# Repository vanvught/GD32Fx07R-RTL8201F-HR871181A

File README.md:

# GD32Fx07R development board with RTL8201F and HR871181A

This board can be used with the `GD32F107Rx` , `GD32F207Rx`, `GD32F407Rx` MCU's. 

More information [https://www.gd32-dmx.org/dev-board.html](https://www.gd32-dmx.org/dev-board.html)

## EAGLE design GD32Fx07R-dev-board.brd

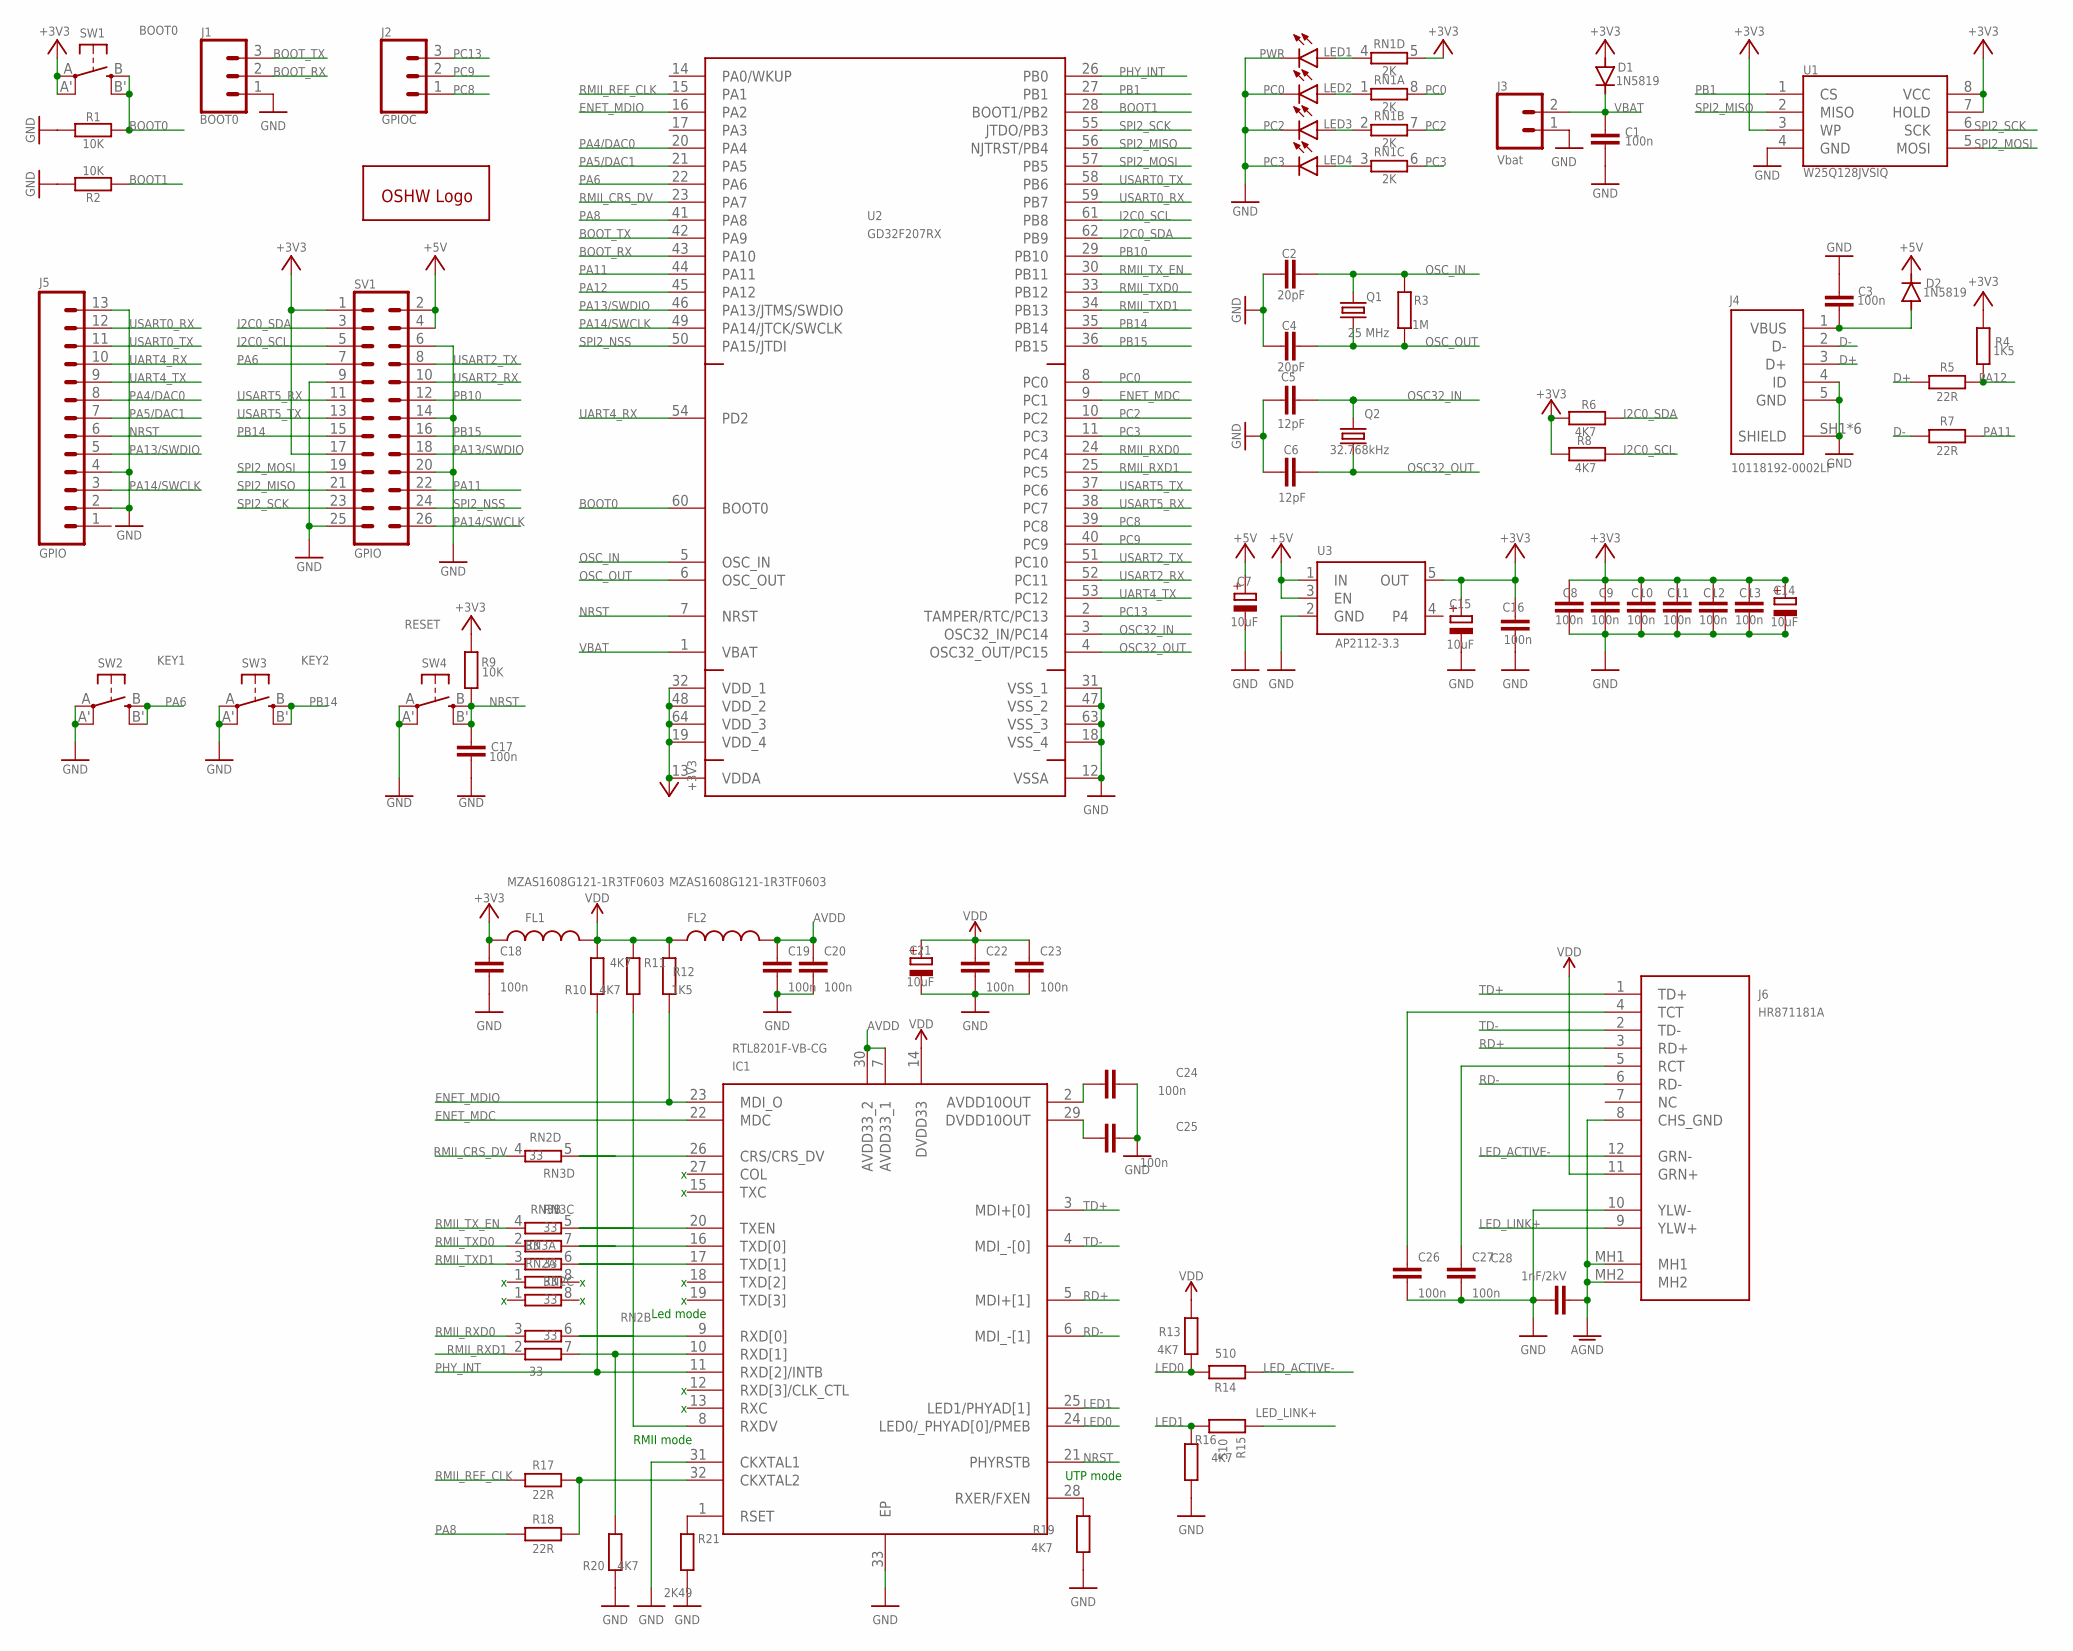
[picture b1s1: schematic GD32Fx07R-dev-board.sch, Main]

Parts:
C1, C3, C8, C9, C10, C11, C12, C13, C16, C17, C18, C19, C20, C22, C23, C24, C25, C26, C27: 100n; C0603; JLCPCB C14663
C2, C4: 20pF; C0603; JLCPCB C38523
C5, C6: 12pF; C0603; JLCPCB C38523
C7, C14, C15, C21: 10uF; A/3216-18R; JLCPCB C7171
C28: 1nF/2kV; C1206; JLCPCB C9196
D1, D2: 1N5819; SOD323-R; JLCPCB C191023
FL1, FL2: MZAS1608G121-1R3TF0603; 0603
GOLD_ORB_SM1: OSHWLOGOLOGO5MM; OSHW_5MM
IC1: RTL8201F-VB-CG; QFN50P500X500X100-33N
J1: BOOT0; 1X03
J2: GPIOC; 1X03
J3: Vbat; 1X02_NO_SILK
J4: 10118192-0002LF; JLCPCB C2972784
J5: GPIO; 1X13
J6: HR871181A
LED1: PWR; CHIP-LED0603; JLCPCB C72043
LED2: PC0; CHIP-LED0603; JLCPCB C72043
LED3: PC2; CHIP-LED0603; JLCPCB C72043
LED4: PC3; CHIP-LED0603; JLCPCB C72043
Q1: 25 MHz; CSM-7X-DU; JLCPCB C14872
Q2: 32.768kHz; 3.2X1.5; JLCPCB C32346
R1, R2, R9: 10K; R0603; JLCPCB C25804
R3: 1M; R0603; JLCPCB C22935
R4, R12: 1K5; R0603; JLCPCB C22843
R5, R7, R17, R18: 22R; R0603; JLCPCB C23345
R6, R8, R10, R11, R13, R16, R19, R20: 4K7; R0603; JLCPCB C23162
R14, R15: 510; R0603; JLCPCB C23193
R21: 2K49; R0603; JLCPCB C100897
RN1: 2K; 4X0402ARV341; JLCPCB C44891
RN2, RN3: 33; 4X0402ARV341; JLCPCB C25501
SV1: GPIO; MA13-2
SW1: BOOT0; EVQ-Q2; JLCPCB C221880
SW2: KEY1; EVQ-Q2; JLCPCB C221880
SW3: KEY2; EVQ-Q2; JLCPCB C221880
SW4: RESET; EVQ-Q2; JLCPCB C221880
U1: W25Q128JVSIQ; SO08-EIAJ; JLCPCB C97521
U2: GD32F207RX; LQFP64
U3: AP2112-3.3; SOT23-5; JLCPCB C51118

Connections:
+3V3: C8.1, C9.1, C10.1, C11.1, C12.1, C13.1, C14.+, C15.+, C16.1, C18.1, D1.A, FL1.1, R4.2, R6.2, R8.2, R9.2, RN1.5 (2), SV1.1, SV1.17, SW1.A, SW1.A' (P1), U1.3 (WP), U1.7 (HOLD), U1.8 (VCC), U2.13 (VDDA), U2.19 (VDD_4), U2.32 (VDD_1), U2.48 (VDD_2), U2.64 (VDD_3), U3.5 (OUT)
+5V: C7.+, D2.C, SV1.2, SV1.4, U3.1 (IN), U3.3 (EN)
AGND: C28.2, J6.8 (CHS_GND), J6.MH1, J6.MH2
AVDD: C19.1, C20.1, FL2.2, IC1.7 (AVDD33_1), IC1.30 (AVDD33_2)
BOOT0: R1.2, SW1.B (S), SW1.B' (S1), U2.60 (BOOT0)
BOOT1: R2.1, U2.28 (BOOT1/PB2)
BOOT_RX: J1.2, U2.43 (PA10)
BOOT_TX: J1.3, U2.42 (PA9)
CLOCK: IC1.32 (CKXTAL2), R17.2, R18.2
D+: J4.3 (D+), R5.1
D-: J4.2 (D-), R7.1
ENET_MDC: IC1.22 (MDC), U2.9 (PC1)
ENET_MDIO: IC1.23 (MDI_O), R12.1, U2.16 (PA2)
GND: C1.2, C2.1, C3.1, C4.1, C5.1, C6.1, C7.-, C8.2, C9.2, C10.2, C11.2, C12.2, C13.2, C14.-, C15.-, C16.2, C17.2, C18.2, C19.2, C20.2, C21.-, C22.2, C23.2, C24.1, C25.1, C26.2, C27.2, C28.1, IC1.31 (CKXTAL1), IC1.33 (EP), J1.1, J3.1, J4.4 (ID), J4.5 (GND), J4.SH1 (SHIELD), J4.SH2 (SHIELD), J4.SH3 (SHIELD), J4.SH4 (SHIELD), J4.SH5 (SHIELD), J4.SH6 (SHIELD), J5.2, J5.4, J5.13, J6.10 (YLW-), LED1.C, LED2.C, LED3.C, LED4.C, R1.1, R2.2, R16.1, R19.1, R20.1, R21.2, SV1.6, SV1.9, SV1.14, SV1.20, SV1.25, SW2.A, SW2.A' (P1), SW3.A, SW3.A' (P1), SW4.A, SW4.A' (P1), U1.4 (GND), U2.12 (VSSA), U2.18 (VSS_4), U2.31 (VSS_1), U2.47 (VSS_2), U2.63 (VSS_3), U3.2 (GND)
I2C0_SCL: R8.1, SV1.5, U2.61 (PB8)
I2C0_SDA: R6.1, SV1.3, U2.62 (PB9)
LED0: IC1.24 (LED0/_PHYAD[0]/PMEB), R13.1, R14.2
LED1: IC1.25 (LED1/PHYAD[1]), R15.2, R16.2
LED_ACTIVE-: J6.12 (GRN-), R14.1
LED_LINK+: J6.9 (YLW+), R15.1
unnamed: C24.2, IC1.2 (AVDD10OUT)
unnamed: IC1.1 (RSET), R21.1
unnamed: IC1.8 (RXDV), R11.2
unnamed: C25.2, IC1.29 (DVDD10OUT)
unnamed: IC1.28 (RXER/FXEN), R19.2
unnamed: C27.1, J6.5 (RCT)
unnamed: LED2.A, RN1.1
unnamed: LED3.A, RN1.2 (1)
unnamed: C26.1, J6.4 (TCT)
unnamed: LED4.A, RN1.3 (1)
unnamed: LED1.A, RN1.4 (1)
NRST: C17.1, IC1.21 (PHYRSTB), J5.6, R9.1, SW4.B (S), SW4.B' (S1), U2.7 (NRST)
OSC32_IN: C5.2, Q2.2, U2.3 (OSC32_IN/PC14)
OSC32_OUT: C6.2, Q2.1, U2.4 (OSC32_OUT/PC15)
OSC_IN: C2.2, Q1.2, R3.1, U2.5 (OSC_IN)
OSC_OUT: C4.2, Q1.1, R3.2, U2.6 (OSC_OUT)
PA4/DAC0: J5.8, U2.20 (PA4)
PA5/DAC1: J5.7, U2.21 (PA5)
PA6: SV1.7, SW2.B (S), SW2.B' (S1), U2.22 (PA6)
PA8: R18.1, U2.41 (PA8)
PA11: R7.2, SV1.22, U2.44 (PA11)
PA12: R4.1, R5.2, U2.45 (PA12)
PA13/SWDIO: J5.5, SV1.18, U2.46 (PA13/JTMS/SWDIO)
PA14/SWCLK: J5.3, SV1.26, U2.49 (PA14/JTCK/SWCLK)
PB1: U1.1 (CS), U2.27 (PB1)
PB10: SV1.12, U2.29 (PB10)
PB14: SV1.15, SW3.B (S), SW3.B' (S1), U2.35 (PB14)
PB15: SV1.16, U2.36 (PB15)
PC0: RN1.8 (2), U2.8 (PC0)
PC2: RN1.7 (2), U2.10 (PC2)
PC3: RN1.6 (2), U2.11 (PC3)
PC8: J2.1, U2.39 (PC8)
PC9: J2.2, U2.40 (PC9)
PC13: J2.3, U2.2 (TAMPER/RTC/PC13)
PHY_INT: IC1.11 (RXD[2]/INTB), R10.1, U2.26 (PB0)
RD+: IC1.5 (MDI+[1]), J6.3 (RD+)
RD-: IC1.6 (MDI_-[1]), J6.6 (RD-)
RMII_CRS_DV: RN2.4 (1), U2.23 (PA7)
RMII_REF_CLK: R17.1, U2.15 (PA1)
RMII_RXD0: RN2.3 (1), U2.24 (PC4)
RMII_RXD1: RN2.2 (1), U2.25 (PC5)
RMII_TXD0: RN3.2 (1), U2.33 (PB12)
RMII_TXD1: RN3.3 (1), U2.34 (PB13)
RMII_TX_EN: RN3.4 (1), U2.30 (PB11)
RXD0: IC1.9 (RXD[0]), RN2.6 (2)
RXD1: IC1.10 (RXD[1]), R20.2, RN2.7 (2)
RXDV: IC1.26 (CRS/CRS_DV), RN2.5 (2)
SPI2_MISO: SV1.21, U1.2 (MISO), U2.56 (NJTRST/PB4)
SPI2_MOSI: SV1.19, U1.5 (MOSI), U2.57 (PB5)
SPI2_NSS: SV1.24, U2.50 (PA15/JTDI)
SPI2_SCK: SV1.23, U1.6 (SCK), U2.55 (JTDO/PB3)
TD+: IC1.3 (MDI+[0]), J6.1 (TD+)
TD-: IC1.4 (MDI_-[0]), J6.2 (TD-)
TXD0: IC1.16 (TXD[0]), RN3.7 (2)
TXD1: IC1.17 (TXD[1]), RN3.6 (2)
TXEN: IC1.20 (TXEN), RN3.5 (2)
UART4_RX: J5.10, U2.54 (PD2)
UART4_TX: J5.9, U2.53 (PC12)
USART0_RX: J5.12, U2.59 (PB7)
USART0_TX: J5.11, U2.58 (PB6)
USART2_RX: SV1.10, U2.52 (PC11)
USART2_TX: SV1.8, U2.51 (PC10)
USART5_RX: SV1.11, U2.38 (PC7)
USART5_TX: SV1.13, U2.37 (PC6)
VBAT: C1.1, D1.C, J3.2, U2.1 (VBAT)
VBUS: C3.2, D2.A, J4.1 (VBUS)
VDD: C21.+, C22.1, C23.1, FL1.2, FL2.1, IC1.14 (DVDD33), J6.11 (GRN+), R10.2, R11.1, R12.2, R13.2

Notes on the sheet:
RMII mode
UTP mode
Led mode

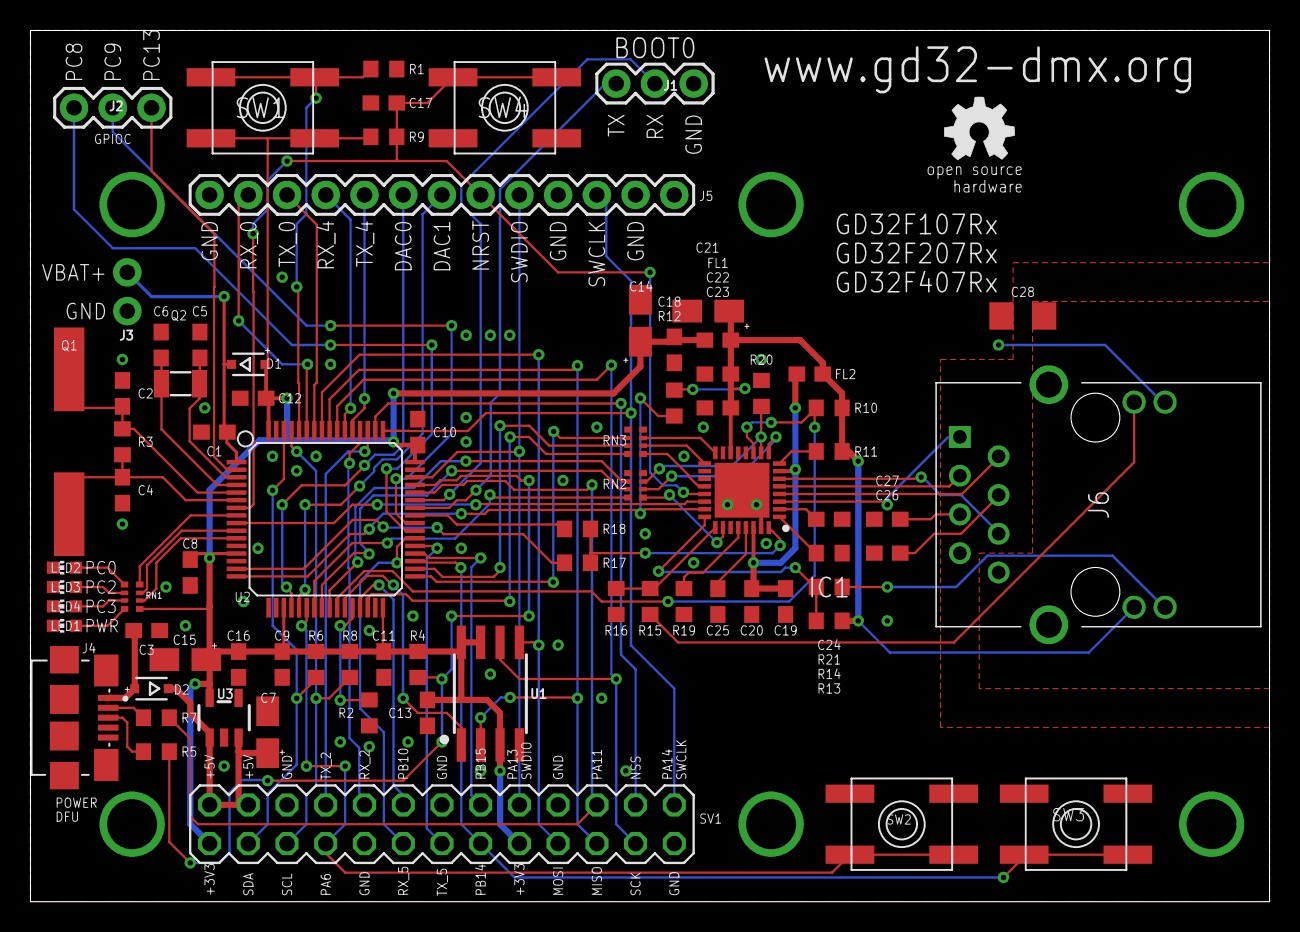
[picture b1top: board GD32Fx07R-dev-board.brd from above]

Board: 2 copper layers, 81.3 x 57.1 mm, 78 parts (0 on the bottom side), 87 nets.

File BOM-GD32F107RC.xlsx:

Qty | Designator | Footprint | Comment | LCSC Part #
19 | C1, C3, C8, C9, C10, C11, C12, C13, C16, C17, C18, C19, C20, C22, C23, C24, C25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 | C0603 | 100n | C14663
2 | C2, C4 | C0603 | 20pF | C38523
1 | C28 | C1206 | 1nF/2kV | C9196
2 | C5, C6 | C0603 | 12pF | C38523
4 | C7, C14, C15, C21 | A/3216-18R | 10uF | C7171
2 | D1, D2 | SOD323-R | 1N5819 | C191023
2 | FL1, FL2 | 603 | MZAS1608G121-1R3TF0603 | C709642
1 | IC1 | QFN50P500X500X100-33N | RTL8201F-VB-CG | C45044
1 | J4 | 10118192-0002LF | 10118192-0002LF | C2972784
1 | J6 | HR871181A | HR871181A | C49312
1 | LED1 | CHIP-LED0603 | PWR | C72043
1 | LED2 | CHIP-LED0603 | PC0 | C72043
1 | LED3 | CHIP-LED0603 | PC2 | C72043
1 | LED4 | CHIP-LED0603 | PC3 | C72043
1 | Q1 | CSM-7X-DU | 25 MHz | C14872
1 | Q2 | 3.2X1.5 | 32.768kHz | C32346
3 | R1, R2, R9 | R0603 | 10K | C25804
2 | R14, R15 | R0603 | 510 | C23193
1 | R21 | R0603 | 2K49 | C100897
1 | R3 | R0603 | 1M | C22935
2 | R4, R12 | R0603 | 1K5 | C22843
4 | R5, R7, R17, R18 | R0603 | 22R | C23345
8 | R6, R8, R10, R11, R13, R16, R19, R20 | R0603 | 4K7 | C23162
1 | RN1 | 4X0402ARV341 | 2K | C44891
2 | RN2, RN3 | 4X0402ARV341 | 33 | C25501
1 | SW1 | EVQ-Q2 | BOOT0 | C221880
1 | SW2 | EVQ-Q2 | KEY1 | C221880
1 | SW3 | EVQ-Q2 | KEY2 | C221880
1 | SW4 | EVQ-Q2 | RESET | C221880
1 | U1 | SO08-EIAJ | W25Q128JVSIQ | C97521
1 | U2 | LQFP64 | GD32F107RCT6 | C94285
1 | U3 | SOT23-5 | AP2112-3.3 | C51118
72

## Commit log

2024-03-03 Initial commit
    @particlerain
2025-01-19 Updated BOM
    - Changed led part number

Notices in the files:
parts and their libraries:
SparkFun-Connectors: Licensing: Creative Commons ShareAlike 4.0 International - https://creativecommons.org/licenses/by-sa/4.0
crystal-geyer_V1_0: Copyright: Geyer-Electronic
